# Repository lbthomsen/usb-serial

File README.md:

# usb-serial
CP2102 based USB -> Serial

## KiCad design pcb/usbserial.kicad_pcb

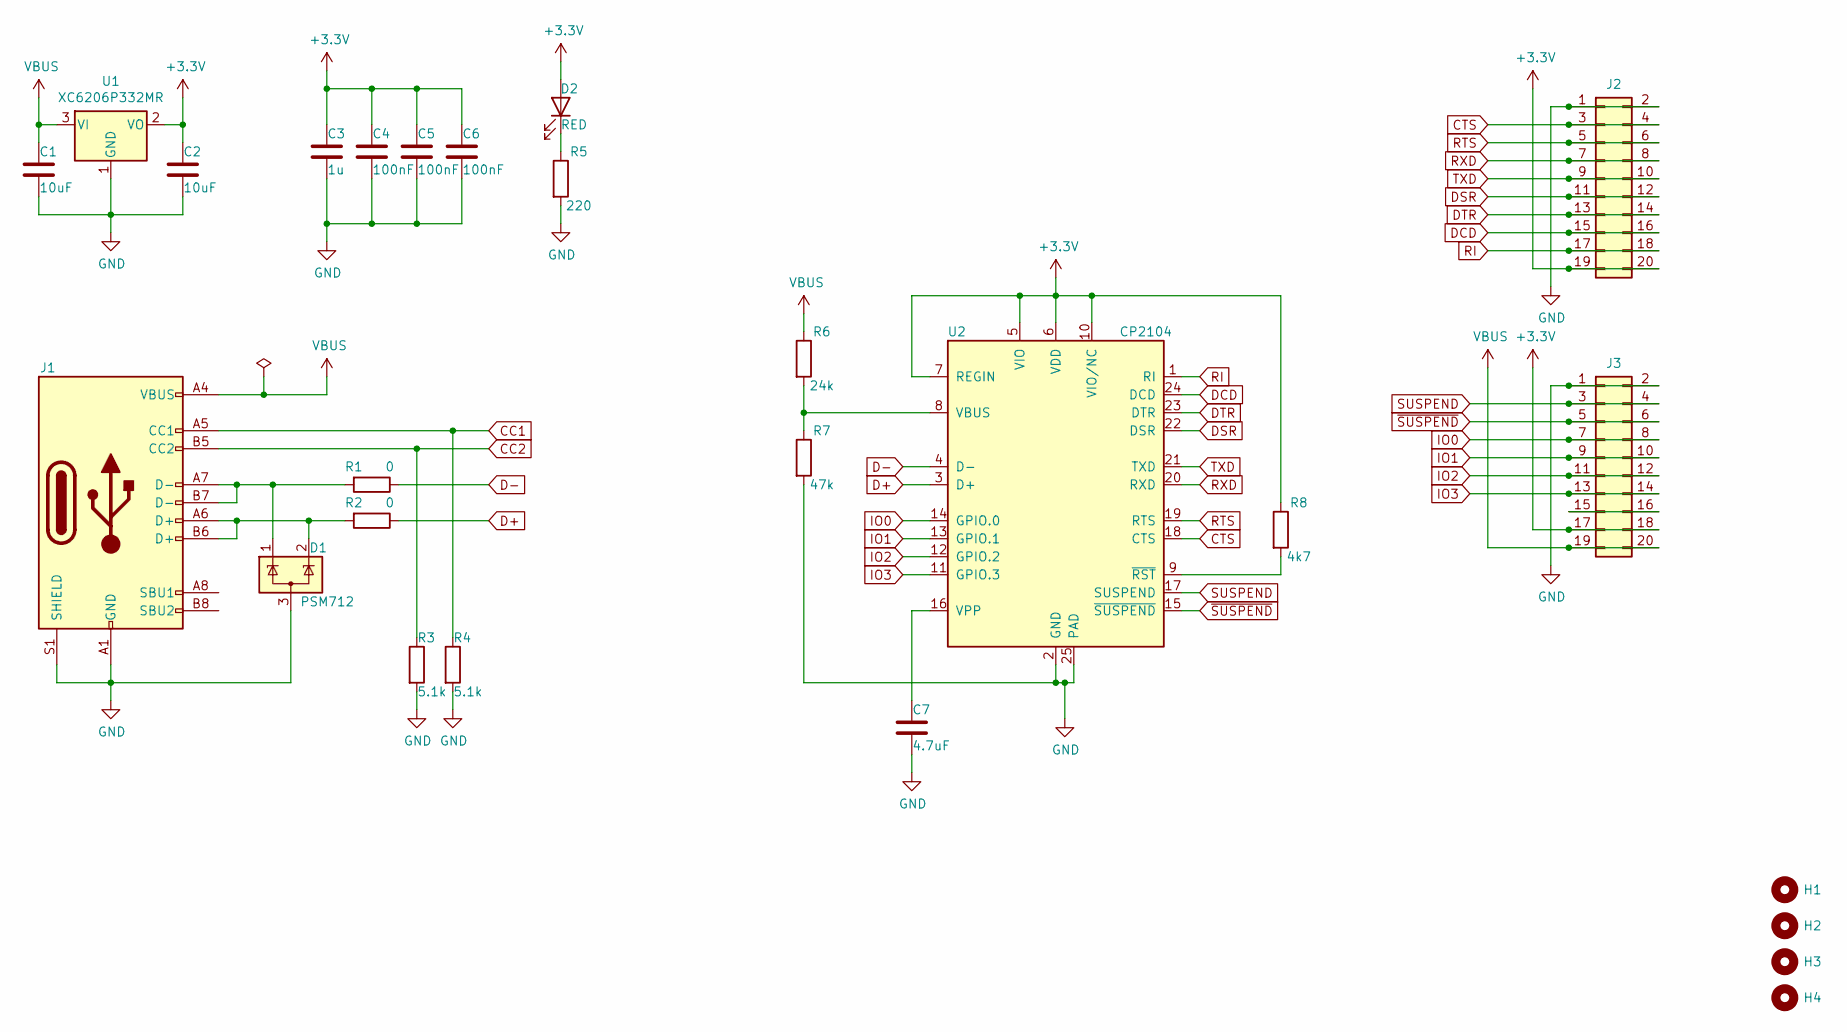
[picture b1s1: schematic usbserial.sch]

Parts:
C1, C2: 10uF; C_0805_2012Metric; LCSC C15850
C3: 1u; C_0402_1005Metric; LCSC C52923
C4, C5, C6: 100nF; C_0402_1005Metric; LCSC C1525
C7: 4.7uF; C_0402_1005Metric; LCSC C23733
D1: PSM712; SOT-23; LCSC C32677
D2: RED; LED_0603_1608Metric; LCSC C2286
H1, H2, H3, H4: MountingHole_2.2mm_M2_ISO7380
J1: USB_C_Receptacle_USB2.0; USB_C_Receptacle_HRO_TYPE-C-31-M-12; LCSCAlt C167321
J2, J3: PinHeader_2x10_P2.54mm_Vertical
R1, R2: 0; R_0603_1608Metric; LCSC C21189
R3, R4: 5.1k; R_0402_1005Metric; LCSC C25905
R5: 220; R_0402_1005Metric; LCSC C25091
R6: 24k; R_0402_1005Metric; LCSC C25769
R7: 47k; R_0402_1005Metric; LCSC C25792
R8: 4k7; R_0402_1005Metric; LCSC C25900
U1: XC6206P332MR; SOT-23; LCSC C5446
U2: CP2104; QFN-24-1EP_4x4mm_P0.5mm_EP2.6x2.6mm

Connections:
+3V3: C2.1, C3.1, C4.1, C5.1, C6.1, D2.2 (A), J2.19, J2.20, J3.17, J3.18, R8.1, U1.2 (VO), U2.5 (VIO), U2.6 (VDD), U2.7 (REGIN), U2.10 (VIO/NC)
CC1: J1.A5 (CC1), R4.1
CC2: J1.B5 (CC2), R3.1
CTS: J2.3, J2.4, U2.18 (CTS)
D+: R2.1, U2.3 (D+)
D-: R1.1, U2.4 (D-)
DCD: J2.15, J2.16, U2.24 (DCD)
DSR: J2.11, J2.12, U2.22 (DSR)
DTR: J2.13, J2.14, U2.23 (DTR)
GND: C1.2, C2.2, C3.2, C4.2, C5.2, C6.2, C7.2, D1.3 (A), J1.A1 (GND), J1.A12 (GND), J1.B1 (GND), J1.B12 (GND), J1.S1 (SHIELD), J2.1, J2.2, J3.1, J3.2, R3.2, R4.2, R5.2, R7.2, U1.1 (GND), U2.2 (GND), U2.25 (PAD)
IO0: J3.7, J3.8, U2.14 (GPIO.0)
IO1: J3.9, J3.10, U2.13 (GPIO.1)
IO2: J3.11, J3.12, U2.12 (GPIO.2)
IO3: J3.13, J3.14, U2.11 (GPIO.3)
unnamed: C7.1, U2.16 (VPP)
unnamed: D1.1 (K), J1.A7 (D-), J1.B7 (D-), R1.2
unnamed: D1.2 (K), J1.A6 (D+), J1.B6 (D+), R2.2
unnamed: D2.1 (K), R5.1
unnamed: J3.15, J3.16
unnamed: R6.2, R7.1, U2.8 (VBUS)
unnamed: R8.2, U2.9 (~RST)
RI: J2.17, J2.18, U2.1 (RI)
RTS: J2.5, J2.6, U2.19 (RTS)
RXD: J2.7, J2.8, U2.20 (RXD)
SUSPEND: J3.3, J3.4, U2.17 (SUSPEND)
TXD: J2.9, J2.10, U2.21 (TXD)
VBUS: C1.1, J1.A4 (VBUS), J1.A9 (VBUS), J1.B4 (VBUS), J1.B9 (VBUS), J3.19, J3.20, R6.1, U1.3 (VI)
~SUSPEND: J3.5, J3.6, U2.15 (~SUSPEND)

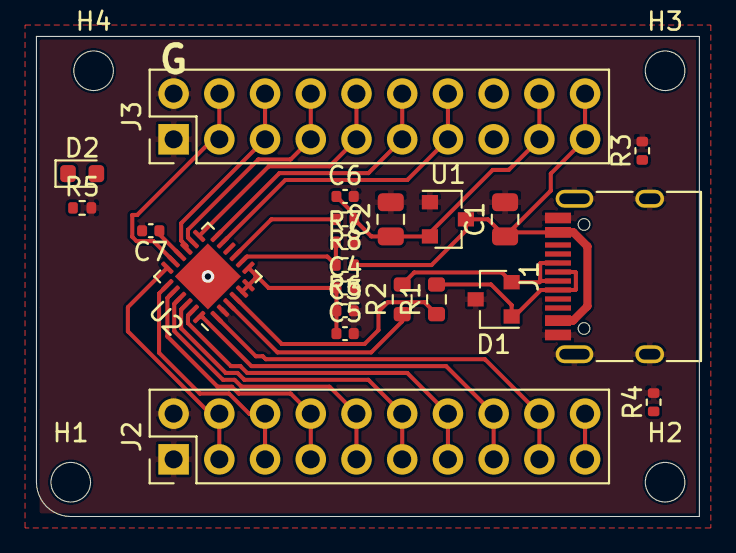
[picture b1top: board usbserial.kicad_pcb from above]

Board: 2 copper layers, 36.8 x 26.7 mm, 26 parts (0 on the bottom side), 28 nets.

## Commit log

2021-03-09 Hmmm
